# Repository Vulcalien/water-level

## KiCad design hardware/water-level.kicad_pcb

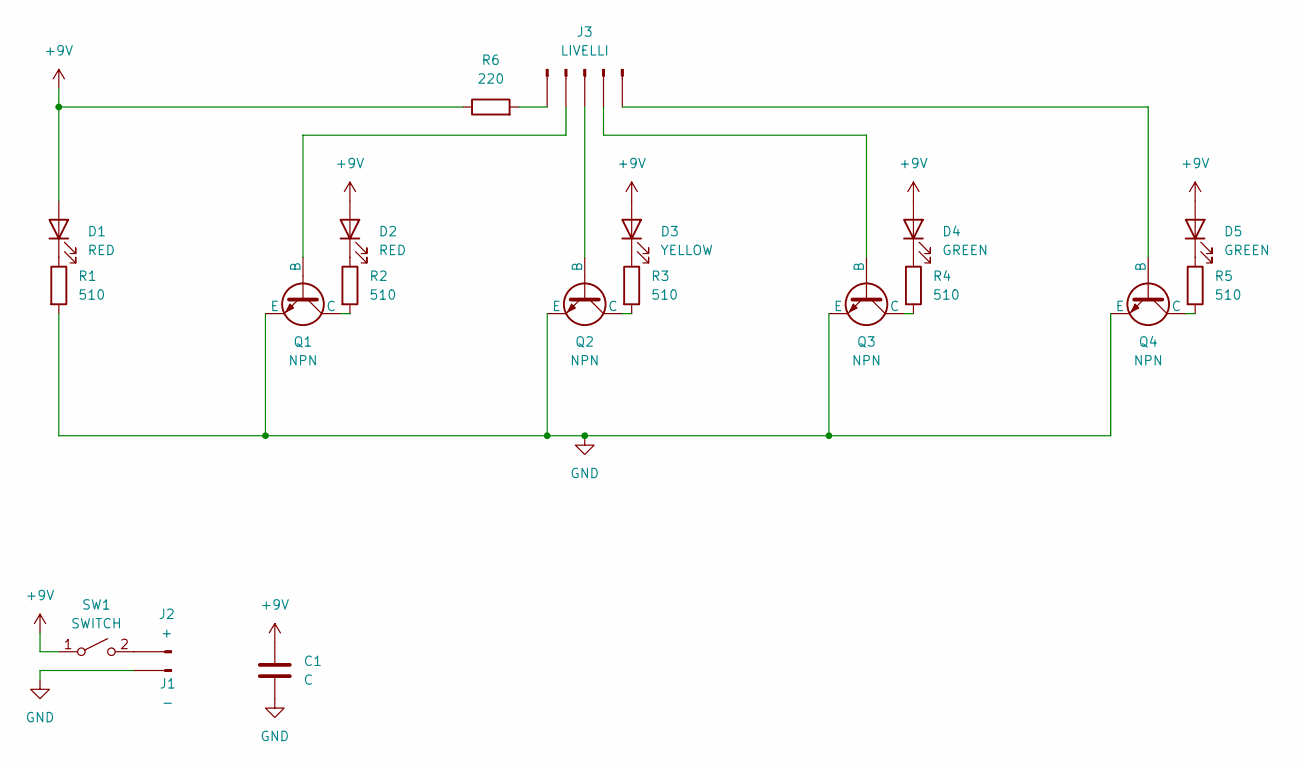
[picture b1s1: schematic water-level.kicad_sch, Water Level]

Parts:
C1: C; C_1206_3216Metric
D1, D2: RED; LED_D5.0mm_FlatTop
D3: YELLOW; LED_D5.0mm_FlatTop
D4, D5: GREEN; LED_D5.0mm_FlatTop
J1: -; PinHeader_1x01_P2.54mm_Vertical
J2: +; PinHeader_1x01_P2.54mm_Vertical
J3: LIVELLI; TerminalBlock_Phoenix_MPT-0,5-5-2.54_1x05_P2.54mm_Horizontal
Q1, Q2, Q3, Q4: NPN; TO-92_Horizontal2
R1, R2, R3, R4, R5: 510; R_1206_3216Metric_Pad1.30x1.75mm_HandSolder
R6: 220; R_Axial_DIN0207_L6.3mm_D2.5mm_P10.16mm_Horizontal
SW1: SWITCH; SW_PUSH_6mm_H7.3mm

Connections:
+9V: C1.2, D1.2 (A), D2.2 (A), D3.2 (A), D4.2 (A), D5.2 (A), R6.1, SW1.1 (A)
GND: C1.1, J1.1 (Pin_1_1), Q1.3 (E), Q2.3 (E), Q3.3 (E), Q4.3 (E), R1.2
unnamed: D1.1 (K), R1.1
unnamed: D2.1 (K), R2.1
unnamed: D3.1 (K), R3.1
unnamed: D4.1 (K), R4.1
unnamed: D5.1 (K), R5.1
unnamed: J2.1 (Pin_1_1), SW1.2 (B)
unnamed: J3.1, Q4.2 (B)
unnamed: J3.2, Q3.2 (B)
unnamed: J3.3, Q2.2 (B)
unnamed: J3.4, Q1.2 (B)
unnamed: J3.5, R6.2
unnamed: Q1.1 (C), R2.2
unnamed: Q2.1 (C), R3.2
unnamed: Q3.1 (C), R4.2
unnamed: Q4.1 (C), R5.2

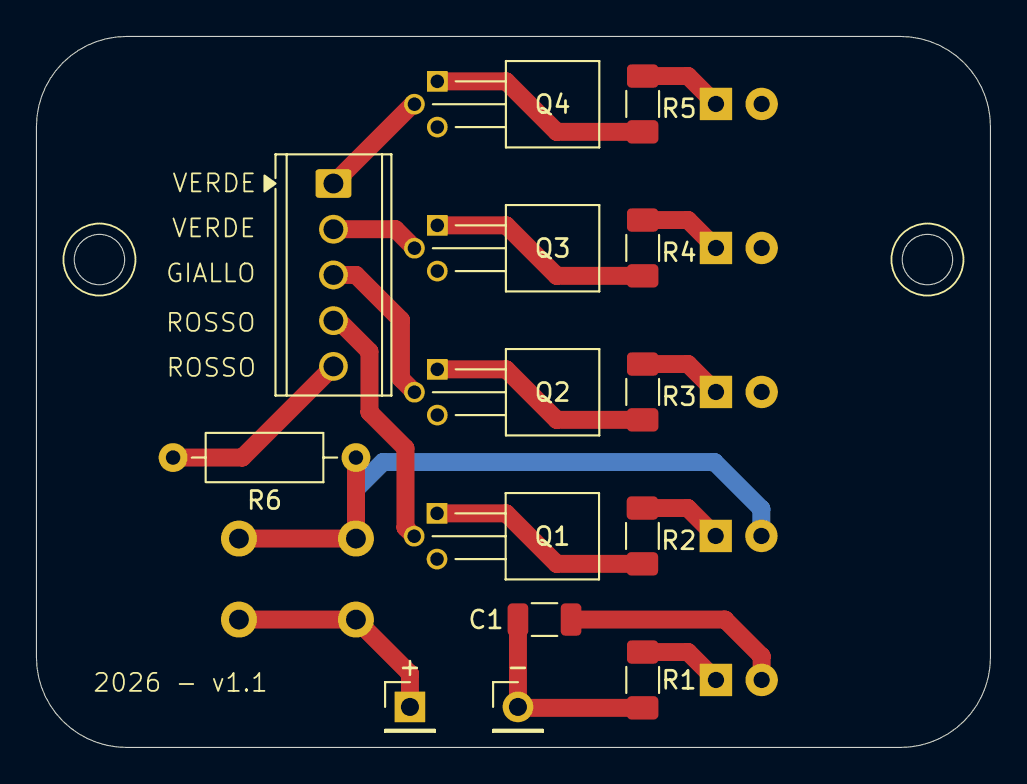
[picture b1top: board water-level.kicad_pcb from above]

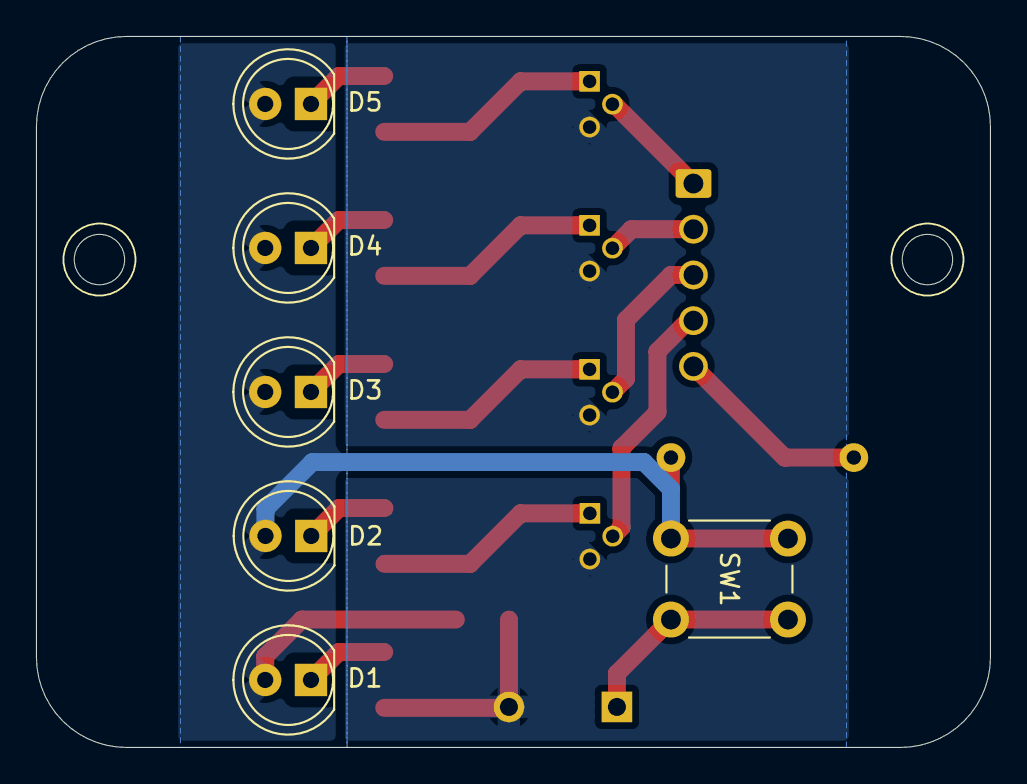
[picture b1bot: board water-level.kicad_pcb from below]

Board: 2 copper layers, 53.0 x 39.5 mm, 20 parts (6 on the bottom side), 17 nets.
